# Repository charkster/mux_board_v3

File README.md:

# mux_board_v3
Custom PCB with SAMD21 QT PY controlling TWO ADG1606BRUZ 16 input muxes!

**--> UPDATED design available: [mux_board_v5](https://github.com/charkster/mux_board_v5) <--**

Check-out my **PDF** [schematic](https://github.com/charkster/mux_board_v3/blob/main/mux_board_v3_schematic.pdf) !!

The SAMD21 QT PY can be  programmed with the qt_py_samd21-usbtmc.uf2 file (drag-n-drop) and has the same USBTMC commands that my [Mux Board V1](https://github.com/charkster/mux_board_v1) had. Here is the list:

**MUX1:EN 1** # enable MUX1, a zero will disable the mux

**MUX1:SEL 1** # select S1 input, values 1 through 16 are valid

**MUX1:EN?** # this query returns the state of MUX1

**MUX1:SEL?** # this query returns the presently selected input

***RST** # disables all MUX enables

***IDN?** # returns valid commands and this URL

2x10 2.54mm stacking headers can be found on [Aliexpress](https://www.aliexpress.us/item/2251832794527968.html?gatewayAdapt=glo2usa4itemAdapt&_randl_shipto=US)

SAMD21 QT PY and ADG1606BRUZ ICs can be found on Digikey/Mouser.

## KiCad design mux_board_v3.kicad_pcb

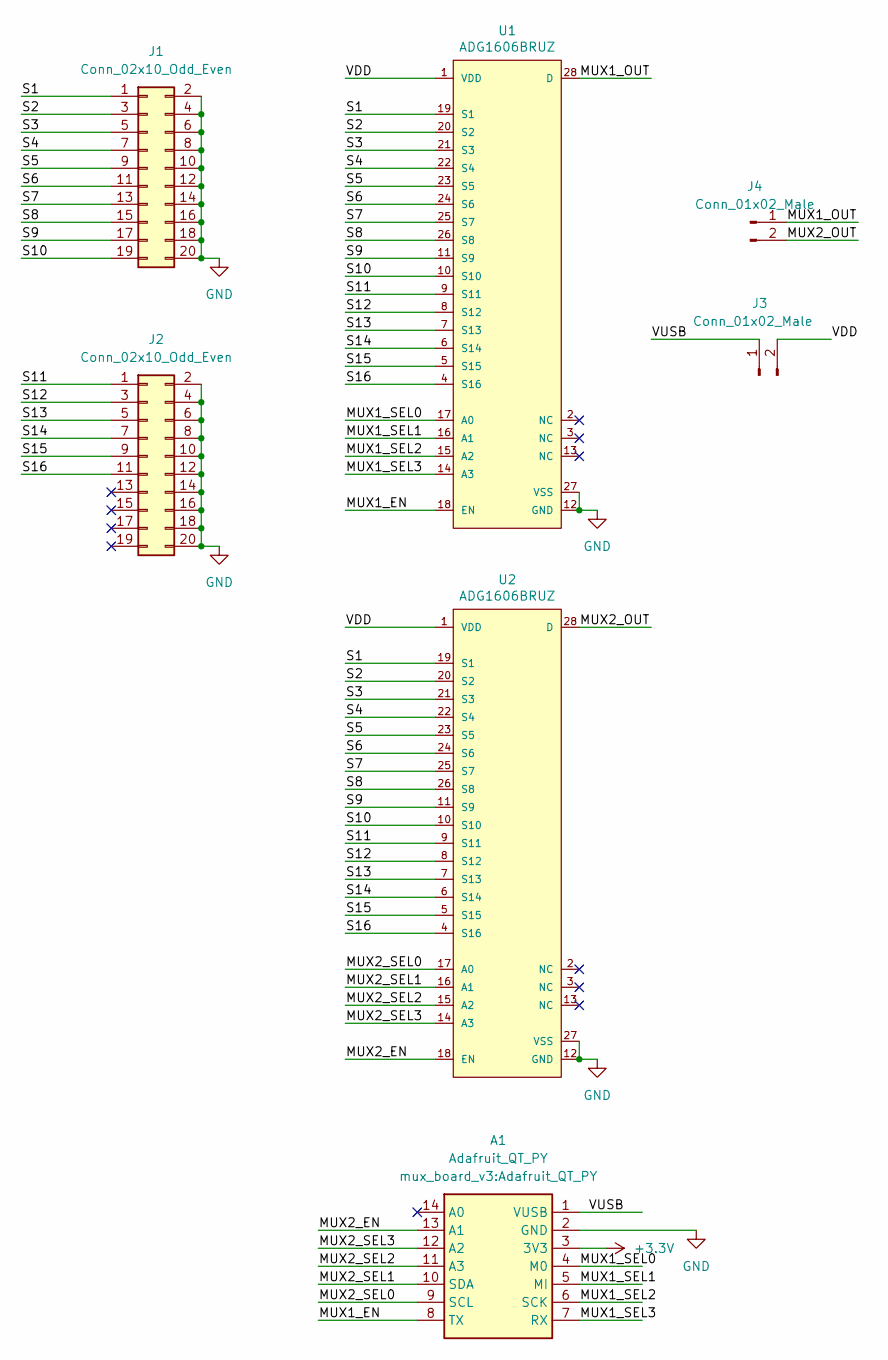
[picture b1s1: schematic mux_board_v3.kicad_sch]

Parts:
A1: Adafruit_QT_PY
J1, J2: Conn_02x10_Odd_Even; PinHeader_2x10_P2.54mm_Vertical
J3, J4: Conn_01x02_Male; PinHeader_1x02_P2.54mm_Vertical
U1, U2: ADG1606BRUZ; Analog_Devices-RU-28-0-0-IPC_A; mouser part number 584-ADG1606BRUZ; digikey description IC MULTIPLEXER 1 X 16 28TSSOP

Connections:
+3V3: A1.3 (3V3)
/MUX1_EN: A1.8 (TX), U1.18 (EN)
/MUX1_OUT: J4.1, U1.28 (D)
/MUX1_SEL0: A1.4 (M0), U1.17 (A0)
/MUX1_SEL1: A1.5 (MI), U1.16 (A1)
/MUX1_SEL2: A1.6 (SCK), U1.15 (A2)
/MUX1_SEL3: A1.7 (RX), U1.14 (A3)
/MUX2_EN: A1.13 (A1), U2.18 (EN)
/MUX2_OUT: J4.2, U2.28 (D)
/MUX2_SEL0: A1.9 (SCL), U2.17 (A0)
/MUX2_SEL1: A1.10 (SDA), U2.16 (A1)
/MUX2_SEL2: A1.11 (A3), U2.15 (A2)
/MUX2_SEL3: A1.12 (A2), U2.14 (A3)
/S1: J1.1, U1.19 (S1), U2.19 (S1)
/S2: J1.3, U1.20 (S2), U2.20 (S2)
/S3: J1.5, U1.21 (S3), U2.21 (S3)
/S4: J1.7, U1.22 (S4), U2.22 (S4)
/S5: J1.9, U1.23 (S5), U2.23 (S5)
/S6: J1.11, U1.24 (S6), U2.24 (S6)
/S7: J1.13, U1.25 (S7), U2.25 (S7)
/S8: J1.15, U1.26 (S8), U2.26 (S8)
/S9: J1.17, U1.11 (S9), U2.11 (S9)
/S10: J1.19, U1.10 (S10), U2.10 (S10)
/S11: J2.1, U1.9 (S11), U2.9 (S11)
/S12: J2.3, U1.8 (S12), U2.8 (S12)
/S13: J2.5, U1.7 (S13), U2.7 (S13)
/S14: J2.7, U1.6 (S14), U2.6 (S14)
/S15: J2.9, U1.5 (S15), U2.5 (S15)
/S16: J2.11, U1.4 (S16), U2.4 (S16)
/VDD: J3.2, U1.1 (VDD), U2.1 (VDD)
/VUSB: A1.1 (VUSB), J3.1
GND: A1.2 (GND), J1.2, J1.4, J1.6, J1.8, J1.10, J1.12, J1.14, J1.16, J1.18, J1.20, J2.2, J2.4, J2.6, J2.8, J2.10, J2.12, J2.14, J2.16, J2.18, J2.20, U1.12 (GND), U1.27 (VSS), U2.12 (GND), U2.27 (VSS)

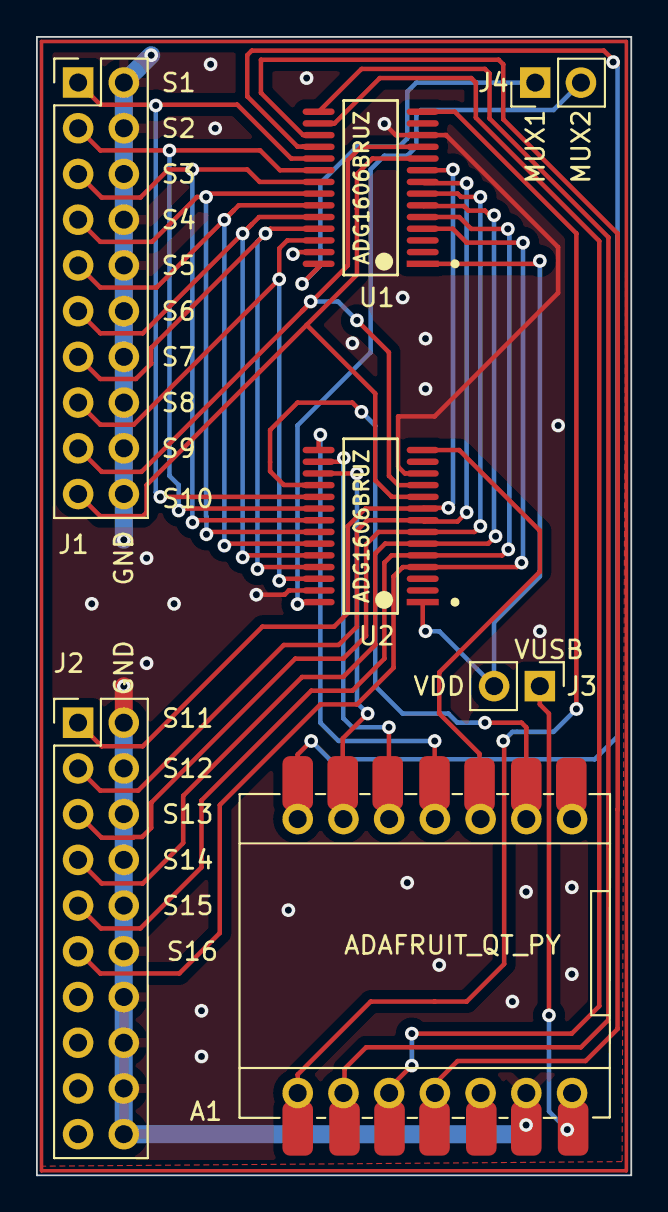
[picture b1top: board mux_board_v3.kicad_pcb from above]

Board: 2 copper layers, 33.0 x 63.2 mm, 7 parts (0 on the bottom side), 31 nets.

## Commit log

2023-04-11 improved picture
2023-04-29 Update README.md
    Corrected description of *RST command
2023-05-04 Update README.md
    added link to mux_board_v5

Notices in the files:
mux_board_v3.kicad_pcb:
creativecommons.org/licenses/by/4.0
License: CC BY 4.0
